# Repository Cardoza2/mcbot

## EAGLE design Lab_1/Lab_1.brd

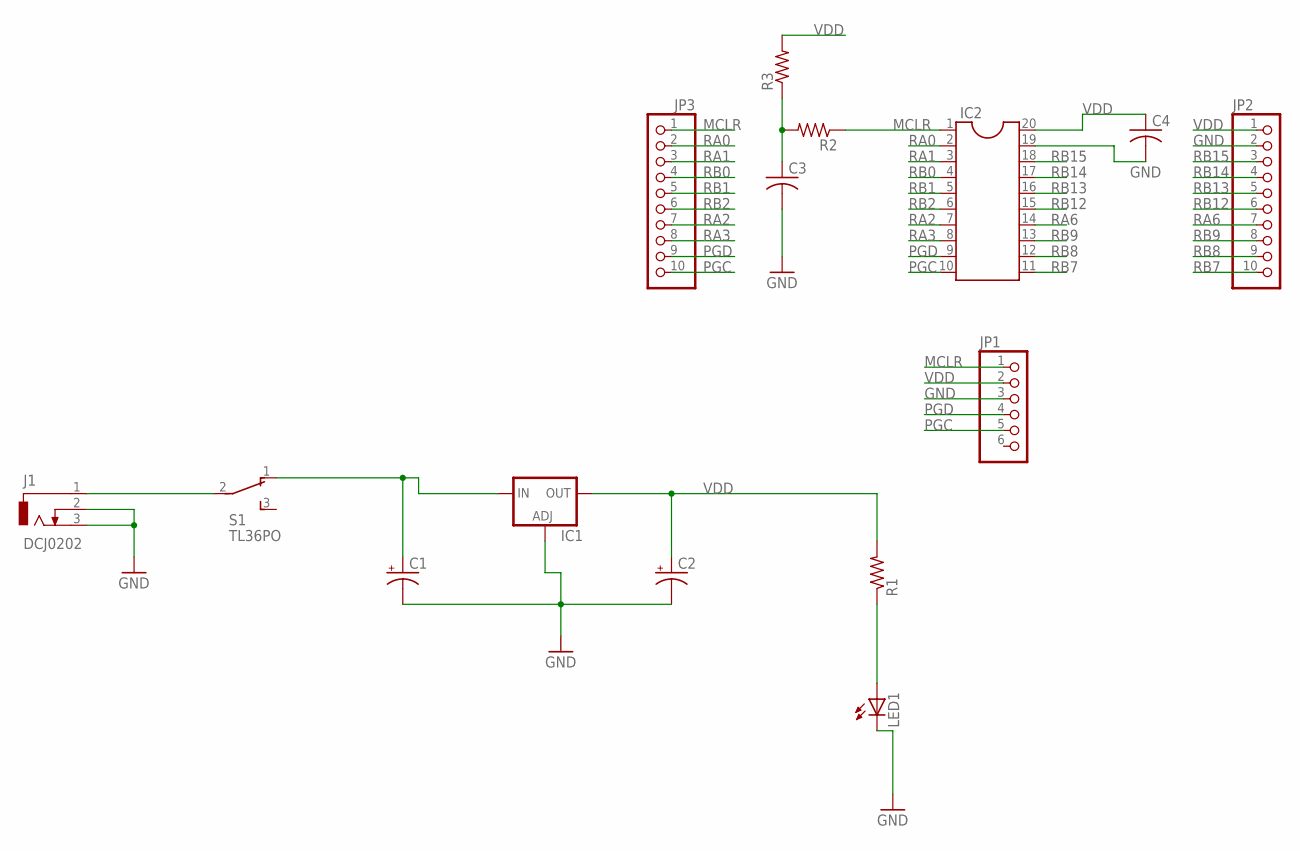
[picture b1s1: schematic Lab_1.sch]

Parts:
C1, C2: CPOL-USE2.5-5; E2,5-5
C3, C4: C-US025-024X044; C025-024X044
IC1: LM317TS; 317TS
IC2: DIL20S; SOCKET-20
J1: DCJ0202
JP1: PINHD-1X6; 1X06
JP2, JP3: PINHD-1X10; 1X10
LED1: LED3MM
R1, R2, R3: R-US_0204/7; 0204/7
S1: TL36PO; TL3XPO

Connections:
GND: C1.-, C2.-, C3.2, C4.2, IC1.1 (ADJ), IC2.19, J1.2, J1.3, JP1.3, JP2.2, LED1.K (C)
MCLR: IC2.1, JP1.1, JP3.1, R2.1
unnamed: J1.1, S1.2
unnamed: C1.+, IC1.3 (IN), S1.1 (O)
unnamed: C3.1, R2.2, R3.1
unnamed: LED1.A, R1.1
PGC: IC2.10, JP1.5, JP3.10
PGD: IC2.9, JP1.4, JP3.9
RA0: IC2.2, JP3.2
RA1: IC2.3, JP3.3
RA2: IC2.7, JP3.7
RA3: IC2.8, JP3.8
RA6: IC2.14, JP2.7
RB0: IC2.4, JP3.4
RB1: IC2.5, JP3.5
RB2: IC2.6, JP3.6
RB7: IC2.11, JP2.10
RB8: IC2.12, JP2.9
RB9: IC2.13, JP2.8
RB12: IC2.15, JP2.6
RB13: IC2.16, JP2.5
RB14: IC2.17, JP2.4
RB15: IC2.18, JP2.3
VDD: C2.+, C4.1, IC1.2 (OUT), IC2.20, JP1.2, JP2.1, R1.2, R3.2

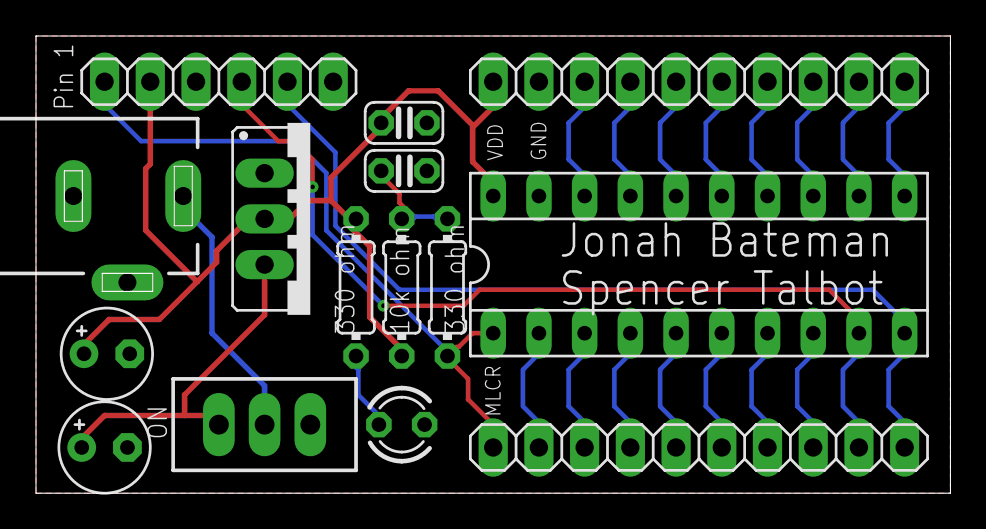
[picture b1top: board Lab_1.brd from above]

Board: 2 copper layers, 50.8 x 25.4 mm, 15 parts (0 on the bottom side), 24 nets.

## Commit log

2018-10-29 adding a Git cheatsheet for reference.
2018-10-29 Created project and main function. Copied IR lab code in and began some simple code changes and comments.
2018-10-30 Updating some of the comments
2018-10-31 Modifying some comments.
2018-11-01 trial2
2018-11-01 Added interrupt file
2018-11-03 Minor edits to interrupt file
2018-11-03 Added testing file and functions for Milestone 8
2018-11-03 Final milestone 8 tweaks
2018-11-08 Added servo functions but still not working
2018-11-08 Working test servo functions
2018-11-10 Broken lifting code
2018-11-17 Moved several functions to respective files and added CNInterrupt functions to testing.c
2018-11-17 Milestone 10 checkpoint 2, added more functions
2018-11-17 Milestone 10 testing
2018-11-17 Working on IRsensor in testing.c"
2018-11-17 PWM CRAP
2018-11-17 Copied lab7 code into testing.c
2018-11-17 PWM CRAP 2
2018-11-17 Added lab 7 to repo
2018-11-17 FREEDOM
2018-11-17 Milestone 10 process added
2018-11-17 Final Milestone 10
2018-11-23 adding trigger LED pins
2018-11-23 Updating bumper pins
2018-11-23 Updated Configpins to full configuration
2018-12-01 Added servo functions
2018-12-01 Added Lab files to Repos
2018-12-01 Adam's experiment code
2018-12-01 Added some possible IR sensor code for the color sensor
2018-12-01 Added some color code for the ir sensor
2018-12-01 Completed servo test code
2018-12-01 more milestone 11 code
2018-12-01 Almost complete milestone 11
2018-12-01 Added bumper functions
2018-12-01 added MS11
2018-12-01 compiles now
2018-12-02 included configPWM1
2018-12-02 sleep pin config
2018-12-02 enums fixed
2018-12-02 testing LED
2018-12-03 Milestone 11
2018-12-06 Experimenting with the lifting stepper. I was using the drive PWM.
2018-12-06 electronics guide
2018-12-07 Fixing electronics guide.
2018-12-08 beginning milestone 12
2018-12-08 milestone 12 skeleton in testing.c
2018-12-08 put in lift tests in experiment.c
2018-12-08 put in lift tests in experiment.c 2
2018-12-08 edits on wiring doc
2018-12-10 Completed milestone 12
2018-12-11 Made Experiment2 to see how the enum and switch statements work with the pic and two leds. It works.
2018-12-11 Created a tenative compcode file
2018-12-11 Did starting phase, modified sort functions to be a while loop, and did sort phase.
2018-12-11 Changed name of findDispenser to findActive, because it finds the active IRLED, and can be used elsewhere. Tweaked the creep function, and the stop function. Tweaked the starting case.
2018-12-12 tweaked sort and senseColor
2018-12-12 tweaked sort and senseColor 2
2018-12-12 IR deets
2018-12-13 after insanity
2018-12-13 crap.c update
